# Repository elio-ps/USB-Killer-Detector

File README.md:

# SENTINELLE — détecteur d'USB Killer

SENTINELLE est une **carte électronique**, pas un logiciel. On y branche un périphérique USB suspect, et elle
l'alimente comme le ferait un ordinateur. Pendant ce temps, elle surveille ses lignes **D+**, **D−** et
**VBUS**. Dès qu'une tension anormale apparaît, positive ou négative, un voyant rouge s'allume et **reste
allumé** jusqu'au RESET. Cette tension anormale est la signature d'un USB Killer : ce type de clé charge des
condensateurs sur le 5 V du port, puis les décharge en haute tension sur les lignes du port.

Le périphérique testé n'est relié à aucun ordinateur. La prise USB-C de la carte ne sert qu'à l'alimenter, et
il n'y a rien à installer.

> **État (octobre 2026) :** la v2 est conçue sous KiCad 10, et l'ERC comme le DRC sont propres. Elle n'est pas
> encore fabriquée, ni testée sur une vraie carte : les seuils ci-dessous sont calculés, pas mesurés.

## Utilisation

1. Alimenter la carte par la prise **USB-C** (chargeur 5 V ou port d'ordinateur) : le voyant orange **PWR**
   et le voyant vert **OK** s'allument.
2. Brancher le périphérique à tester sur la prise **USB-A**.
3. Lire les voyants. Un voyant rouge allumé signale une tension anormale sur la ligne correspondante, et le
   voyant vert s'éteint.
4. Appuyer sur **RESET** (ou débrancher l'alimentation) pour effacer l'alarme.

## Fonctionnement (blocs A à H du schéma)

Le schéma est `sch/usb-killer-detector.kicad_sch`.

| Bloc | Rôle | Composants |
|---|---|---|
| **A. Alimentation USB-C (5 V)** | Prise d'alimentation sans lignes de données. Les résistances CC permettent à un chargeur USB-C de fournir le 5 V. Une diode TVS protège le 5 V | J2 (USB4125, 6 broches), R1/R2 5,1 kΩ, D1 SMAJ5.0A, C1/C2, voyant PWR D2 + R3 |
| **B. Port sous test USB-A et protection VBUS** | Fournit le 5 V au périphérique testé. D3 empêche toute tension de remonter vers l'alimentation, F1 (fusible réarmable de 500 mA) coupe en cas de surcharge, et D4 écrête VBUS | J1 (USB-A), D3 SS34, F1 MF-MSMF050-2, D4 SMAJ5.0A |
| **C. Références de seuil VH / VL** | Pont diviseur sur le 5 V : VH = 2,42 V et VL = 0,76 V. Comme ces références suivent le 5 V, les seuils aussi | R4 51 kΩ, R5 33 kΩ, R6 15 kΩ, C3/C4 |
| **D. Étages d'entrée (fenêtre ±)** | Chaque ligne est ramenée dans la plage 0–5 V par un pont à haute impédance. Exemple pour D+ : 2 × 220 kΩ en 1206 (R7 + R8), puis 220 kΩ vers le 5 V et 120 kΩ vers la masse, ce qui donne X = 0,15 × V + 1,5 V. Une BAT54S protège les comparateurs et un condensateur de 1 nF filtre le signal | D+ : R7–R10, C5, D5 ; D− : R11–R14, C6, D6 ; VBUS : R15–R17, C7, D7 |
| **E. Comparateurs LM339** | Deux comparateurs par ligne, l'un pour « trop haut » (X > VH), l'autre pour « trop bas » (X < VL). Leurs sorties à collecteur ouvert sont reliées par paires : l'alarme de chaque ligne est active à l'état bas | U1 (D+, D−), U2 (VBUS + commande du voyant OK ; le 8ᵉ comparateur est inutilisé, entrées fixées) |
| **F. Mémoire d'alarme 74HC279** | Trois bascules R/S. Une alarme, même très brève, fait basculer la sortie Q de la ligne à 1, et elle y reste jusqu'au reset | U3 |
| **G. Voyants** | Chaque sortie Q allume sa LED rouge. Un OU à diodes regroupe les trois alarmes et, par un comparateur de U2, éteint la LED verte | D9/D10/D11 + R22–R24, D12–D14, R25, D15 + R26 |
| **H. Découplage, pull-ups, reset** | 100 nF par circuit intégré et pull-ups des alarmes. Reset à la mise sous tension (R21/C11), décharge de C11 par D8 quand on débranche, bouton RESET | C8–C10, R18–R20, R21, C11, D8, SW1 |

Sur D+ et D−, les entrées présentent environ 440 kΩ : la carte n'absorbe donc pas l'énergie d'une décharge.
Sous −200 V, chaque résistance 1206 voit environ 100 V. Sur le PCB, ces lignes ont 1 mm d'isolation jusqu'aux
résistances d'entrée (règles dans `sch/usb-killer-detector.kicad_dru`).

## Seuils d'alarme

| Ligne | Alarme si | Valeurs calculées |
|---|---|---|
| D+ et D− | **> +6,2 V** ou **< −5 V** | +6,16 V / −4,95 V |
| VBUS | **> +6,3 V** ou **< −0,3 V** | +6,34 V / −0,31 V |

Une ligne USB 2.0 normale ne dépasse pas 3,6 V sur D+/D−, et VBUS reste entre 4,75 et 5,25 V. Le seuil VBUS se
règle avec R16/R17. Calculés avec des résistances à ±1 %, les seuils de D+/D− restent dans une fenêtre d'environ
±0,35 V (voir `docs/bom-jlcpcb.md`). Pour les mesurer sur une carte réelle, suivre
[docs/protocole-test.md](docs/protocole-test.md).

## Voyants

| Voyant | Couleur | Signification |
|---|---|---|
| PWR (D2) | orange | Carte alimentée |
| OK (D15) | vert | Aucune alarme mémorisée |
| D+ (D9) | rouge | Tension anormale vue sur D+ (mémorisée) |
| D− (D10) | rouge | Tension anormale vue sur D− (mémorisée) |
| VBUS (D11) | rouge | Tension anormale vue sur VBUS (mémorisée) |

## Reset

Une alarme reste affichée même si l'anomalie n'a duré qu'un instant : rien ne passe inaperçu en cas de
manque d'attention. Pour l'effacer :
- appuyer sur **RESET** (SW1) : une fois le boîtier mis à jour, on l'atteint avec un trombone par le trou du couvercle ;
- ou débrancher l'alimentation : au rebranchement, les alarmes repartent à zéro.

Si la cause est toujours présente au moment du RESET, l'alarme se rallume aussitôt.

## Fabrication (`sch/production/`)

Ces fichiers sont générés par le plugin KiCad **Fabrication Toolkit** (réglages dans `sch/fabrication-toolkit-options.json`).

| Fichier | Contenu |
|---|---|
| `usb-killer-detector.zip` | Gerber et perçages : **à téléverser chez JLCPCB** |
| `bom.csv` | BOM au format JLCPCB, avec les numéros LCSC vérifiés (LED comprises) : **à téléverser** |
| `positions.csv` | Positions des composants, rotations déjà corrigées pour JLC : **à téléverser** |
| `designators.csv`, `netlist.ipc` | Fichiers annexes du plugin |
| `bom-JLCPCB Assembly Order.xls` | Rapport de rapprochement exporté depuis le site JLC lors d'un premier essai. **Périmé** : il propose encore des 220 kΩ à ±5 % et ne trouve pas les LED. Se fier à `bom.csv` |

Les numéros LCSC sont stockés dans le champ `LCSC Part #` de chaque composant, dans le schéma comme dans le PCB.
Le plugin les reprend donc à chaque régénération. Les rapports ERC et DRC de `kicad-cli` sont dans `sch/rapports/`.

Carte : 2 couches, 44 × 82 mm, 1,6 mm d'épaisseur. **Tout est soudé par le fabricant**, y compris les 5 LED de
5 mm traversantes : il faut donc commander l'assemblage des composants traversants. Choix des références : `docs/bom-jlcpcb.md`.

## Boîtier (`PCB/`)

`PCB/Case/Case.FCStd` et `Lid.FCStd` (FreeCAD), `PCB/Model.3mf` pour l'impression, et
`PCB/SENTINELLE-v2-PCB.step` (modèle 3D de la carte). La vérification des découpes par rapport à la v2 est dans
`docs/boitier-v2.md`.

Le boîtier est à jour pour la v2 : fente USB-A, ouverture USB-C, 5 trous de LED avec tubes guide-lumière, trou
RESET et dégagements sous les broches. Il n'a pas encore été imprimé. Au montage, on retourne le couvercle autour
de son grand axe, encoche de la lèvre côté USB-A.

## Démo

> TODO : vidéo de la carte v2 en fonctionnement.

[`demo.gif`](demo.gif) (30 Mo) montre le **prototype sur breadboard** (v1), testé à l'alimentation de labo.

## Sécurité

Ne jamais brancher la prise USB-A de SENTINELLE sur un ordinateur. Ne pas toucher la carte pendant un test :
la haute tension d'un USB Killer est présente sur la prise USB-A et sur les résistances d'entrée. La validation
se fait sans vrai USB Killer, à l'alimentation de labo (voir le protocole de test).

## Équipe

- Elio Pironneau-Sauranus
- Lucas Rios
- Lenny Gaillard
- Evan Siby

Merci à **Philippe Mege**.

## Licence

GNU GPL v3.0 — voir [LICENSE](LICENSE).

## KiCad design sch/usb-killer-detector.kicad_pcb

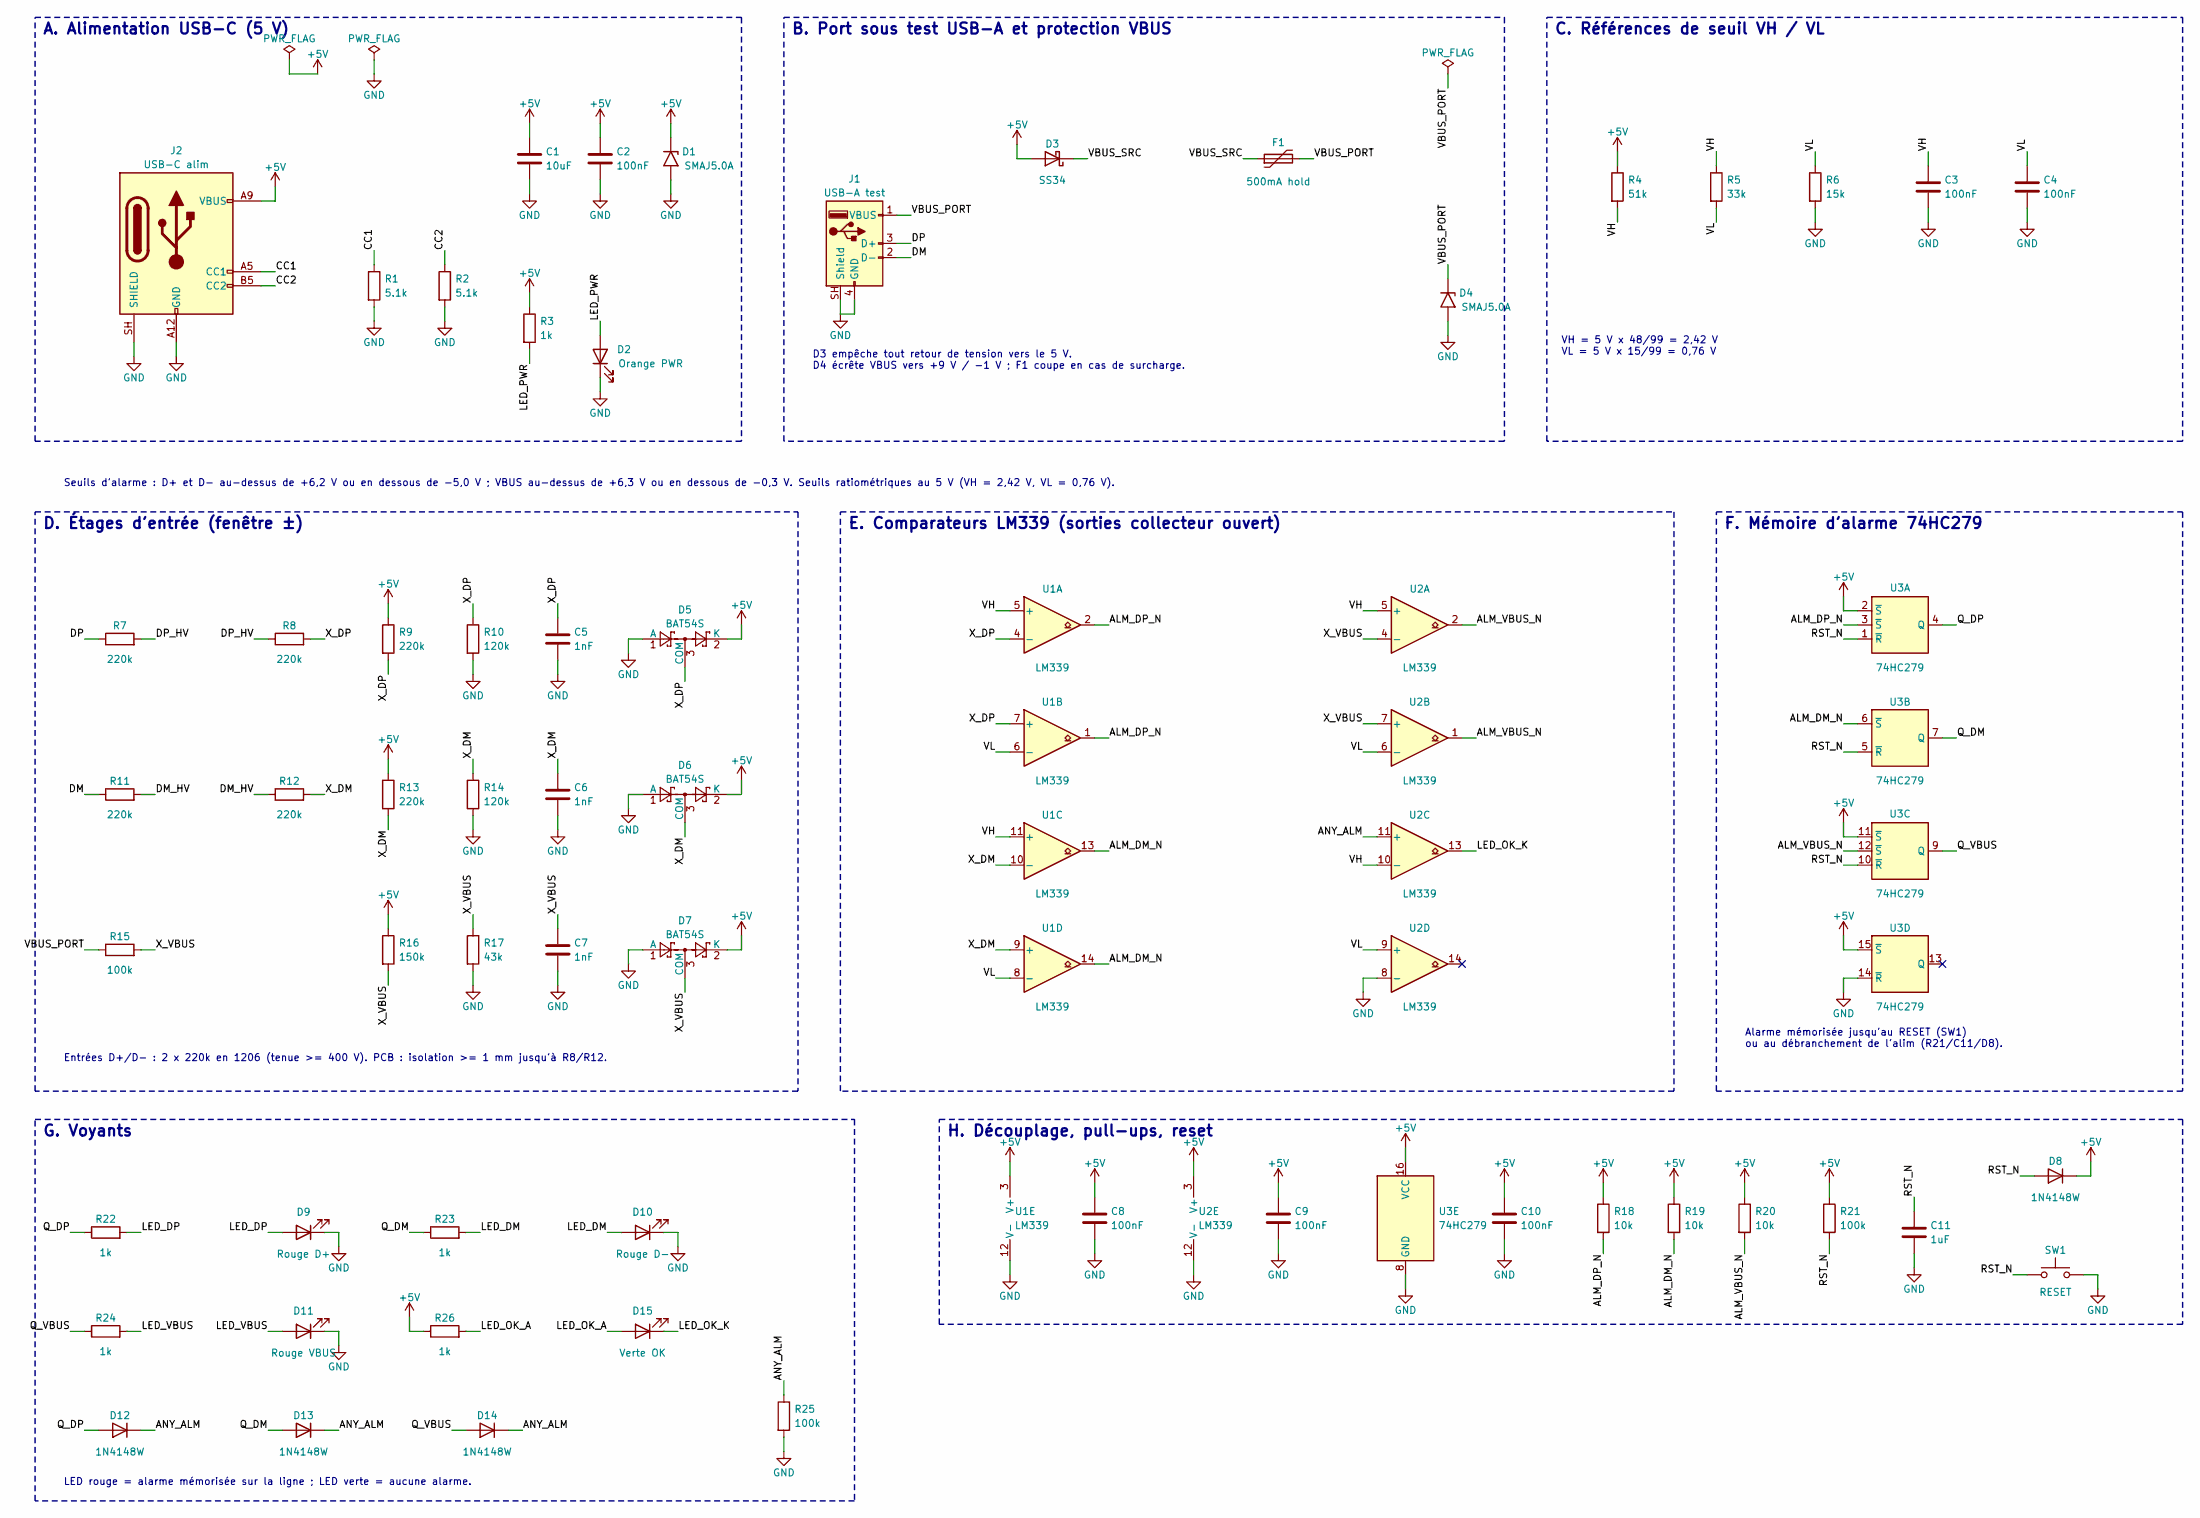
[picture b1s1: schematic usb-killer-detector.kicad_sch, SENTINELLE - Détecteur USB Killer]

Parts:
C1: 10uF; C_0805_2012Metric; LCSC Part # C15850
C2, C3, C4, C8, C9, C10: 100nF; C_0805_2012Metric; LCSC Part # C49678
C5, C6, C7: 1nF; C_0805_2012Metric; LCSC Part # C46653
C11: 1uF; C_0805_2012Metric; LCSC Part # C28323
D1, D4: SMAJ5.0A; D_SMA; MPN SMAJ5.0A; LCSC Part # C113952
D2: Orange PWR; LED_D5.0mm; LCSC Part # C52034657
D3: SS34; D_SMA; MPN SS34; LCSC Part # C8678
D5, D6, D7: BAT54S; SOT-23; MPN BAT54S; LCSC Part # C47546
D8, D12, D13, D14: 1N4148W; D_SOD-123; MPN 1N4148W; LCSC Part # C81598
D9: Rouge D+; LED_D5.0mm; LCSC Part # C87271
D10: Rouge D-; LED_D5.0mm; LCSC Part # C87271
D11: Rouge VBUS; LED_D5.0mm; LCSC Part # C87271
D15: Verte OK; LED_D5.0mm; LCSC Part # C2895548
F1: 500mA hold; Fuse_1812_4532Metric; MPN Bourns MF-MSMF050-2; LCSC Part # C17313
J1: USB-A test; USB_A_Receptacle_GCT_USB1046; MPN GCT USB1046; LCSC Part # C6307429
J2: USB-C alim; USB_C_Receptacle_GCT_USB4125-xx-x_6P_TopMnt_Horizontal; MPN GCT USB4125-GF-A; LCSC Part # C3151650
R1, R2: 5.1k; R_0805_2012Metric; LCSC Part # C27834
R3, R22, R23, R24, R26: 1k; R_0805_2012Metric; LCSC Part # C17513
R4: 51k; R_0805_2012Metric; LCSC Part # C17737
R5: 33k; R_0805_2012Metric; LCSC Part # C17633
R6: 15k; R_0805_2012Metric; LCSC Part # C17475
R7, R8, R11, R12: 220k; R_1206_3216Metric; LCSC Part # C873512
R9, R13: 220k; R_0805_2012Metric; LCSC Part # C17556
R10, R14: 120k; R_0805_2012Metric; LCSC Part # C17436
R15: 100k; R_1206_3216Metric; LCSC Part # C17900
R16: 150k; R_0805_2012Metric; LCSC Part # C17470
R17: 43k; R_0805_2012Metric; LCSC Part # C17695
R18, R19, R20: 10k; R_0805_2012Metric; LCSC Part # C17414
R21, R25: 100k; R_0805_2012Metric; LCSC Part # C149504
SW1: RESET; SW_SPST_B3S-1000; MPN Omron B3S-1000; LCSC Part # C2733655
U1, U2: LM339; SOIC-14_3.9x8.7mm_P1.27mm; MPN LM339DR; LCSC Part # C7948
U3: 74HC279; SOIC-16_3.9x9.9mm_P1.27mm; MPN 74HC279D; LCSC Part # C41430932

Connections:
+5V: C1.1, C2.1, C8.1, C9.1, C10.1, D1.1 (A1), D3.2 (A), D5.2 (K), D6.2 (K), D7.2 (K), D8.1 (K), J2.A9 (VBUS), J2.B9 (VBUS), R3.1, R4.1, R9.1, R13.1, R16.1, R18.1, R19.1, R20.1, R21.1, R26.1, U1.3 (V+), U2.3 (V+), U3.2 (~S), U3.11 (~S), U3.15 (~S), U3.16 (VCC)
/ALM_DM_N: R19.2, U1.13, U1.14, U3.6 (~S)
/ALM_DP_N: R18.2, U1.1, U1.2, U3.3 (~S)
/ALM_VBUS_N: R20.2, U2.1, U2.2, U3.12 (~S)
/ANY_ALM: D12.1 (K), D13.1 (K), D14.1 (K), R25.1, U2.11 (+)
/CC1: J2.A5 (CC1), R1.1
/CC2: J2.B5 (CC2), R2.1
/DM: J1.2 (D-), R11.1
/DM_HV: R11.2, R12.1
/DP: J1.3 (D+), R7.1
/DP_HV: R7.2, R8.1
/LED_DM: D10.2 (A), R23.2
/LED_DP: D9.2 (A), R22.2
/LED_OK_A: D15.2 (A), R26.2
/LED_OK_K: D15.1 (K), U2.13
/LED_PWR: D2.2 (A), R3.2
/LED_VBUS: D11.2 (A), R24.2
/Q_DM: D13.2 (A), R23.1, U3.7 (Q)
/Q_DP: D12.2 (A), R22.1, U3.4 (Q)
/Q_VBUS: D14.2 (A), R24.1, U3.9 (Q)
/RST_N: C11.1, D8.2 (A), R21.2, SW1.1, U3.1 (~R), U3.5 (~R), U3.10 (~R)
/VBUS_PORT: D4.1 (A1), F1.2, J1.1 (VBUS), R15.1
/VBUS_SRC: D3.1 (K), F1.1
/VH: C3.1, R4.2, R5.1, U1.5 (+), U1.11 (+), U2.5 (+), U2.10 (-)
/VL: C4.1, R5.2, R6.1, U1.6 (-), U1.8 (-), U2.6 (-), U2.9 (+)
/X_DM: C6.1, D6.3 (COM), R12.2, R13.2, R14.1, U1.9 (+), U1.10 (-)
/X_DP: C5.1, D5.3 (COM), R8.2, R9.2, R10.1, U1.4 (-), U1.7 (+)
/X_VBUS: C7.1, D7.3 (COM), R15.2, R16.2, R17.1, U2.4 (-), U2.7 (+)
GND: C1.2, C2.2, C3.2, C4.2, C5.2, C6.2, C7.2, C8.2, C9.2, C10.2, C11.2, D1.2 (A2), D2.1 (K), D4.2 (A2), D5.1 (A), D6.1 (A), D7.1 (A), D9.1 (K), D10.1 (K), D11.1 (K), J1.4 (GND), J1.SH (Shield), J2.A12 (GND), J2.B12 (GND), J2.SH (SHIELD), R1.2, R2.2, R6.2, R10.2, R14.2, R17.2, R25.2, SW1.2, U1.12 (V-), U2.8 (-), U2.12 (V-), U3.8 (GND), U3.14 (~R)

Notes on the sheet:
A. Alimentation USB-C (5 V)
B. Port sous test USB-A et protection VBUS
C. Références de seuil VH / VL
D. Étages d'entrée (fenêtre ±)
E. Comparateurs LM339 (sorties collecteur ouvert)
F. Mémoire d'alarme 74HC279
G. Voyants
H. Découplage, pull-ups, reset
Seuils d'alarme : D+ et D- au-dessus de +6,2 V ou en dessous de -5,0 V ; VBUS au-dessus de +6,3 V ou en dessous de -0,3 V. Seuils ratiométriques au 5 V (VH = 2,42 V, VL = 0,76 V).
VH = 5 V x 48/99 = 2,42 V VL = 5 V x 15/99 = 0,76 V
D3 empêche tout retour de tension vers le 5 V. D4 écrête VBUS vers +9 V / -1 V ; F1 coupe en cas de surcharge.
Entrées D+/D- : 2 x 220k en 1206 (tenue >= 400 V). PCB : isolation >= 1 mm jusqu'à R8/R12.
Alarme mémorisée jusqu'au RESET (SW1) ou au débranchement de l'alim (R21/C11/D8).
LED rouge = alarme mémorisée sur la ligne ; LED verte = aucune alarme.

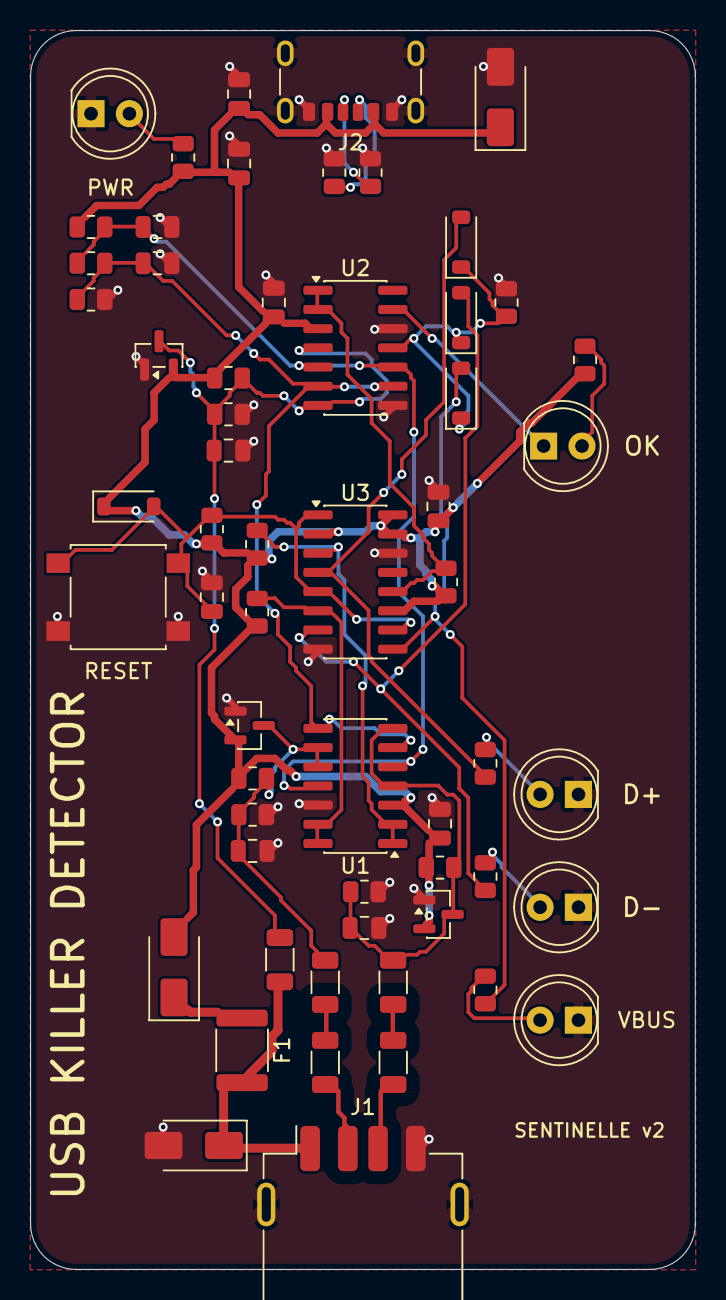
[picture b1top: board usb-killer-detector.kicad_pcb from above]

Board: 2 copper layers, 44.0 x 82.0 mm, 59 parts (0 on the bottom side), 29 nets.

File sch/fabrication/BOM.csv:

"Repere","Valeur","Empreinte","Reference fabricant","Quantite"
"C1","10uF","Capacitor_SMD:C_0805_2012Metric","","1"
"C2,C3,C4,C8,C9,C10","100nF","Capacitor_SMD:C_0805_2012Metric","","6"
"C5,C6,C7","1nF","Capacitor_SMD:C_0805_2012Metric","","3"
"C11","1uF","Capacitor_SMD:C_0805_2012Metric","","1"
"D1,D4","SMAJ5.0A","Diode_SMD:D_SMA","SMAJ5.0A","2"
"D2","Orange PWR","LED_THT:LED_D5.0mm","","1"
"D3","SS34","Diode_SMD:D_SMA","SS34","1"
"D5,D6,D7","BAT54S","Package_TO_SOT_SMD:SOT-23","BAT54S","3"
"D8,D12,D13,D14","1N4148W","Diode_SMD:D_SOD-123","1N4148W","4"
"D9","Rouge D+","LED_THT:LED_D5.0mm","","1"
"D10","Rouge D-","LED_THT:LED_D5.0mm","","1"
"D11","Rouge VBUS","LED_THT:LED_D5.0mm","","1"
"D15","Verte OK","LED_THT:LED_D5.0mm","","1"
"F1","500mA hold","Fuse:Fuse_1812_4532Metric","Bourns MF-MSMF050-2","1"
"J1","USB-A test","Connector_USB:USB_A_Receptacle_GCT_USB1046","GCT USB1046","1"
"J2","USB-C alim","Connector_USB:USB_C_Receptacle_GCT_USB4125-xx-x_6P_TopMnt_Horizontal","GCT USB4125-GF-A","1"
"R1,R2","5.1k","Resistor_SMD:R_0805_2012Metric","","2"
"R3,R22,R23,R24,R26","1k","Resistor_SMD:R_0805_2012Metric","","5"
"R4","51k","Resistor_SMD:R_0805_2012Metric","","1"
"R5","33k","Resistor_SMD:R_0805_2012Metric","","1"
"R6","15k","Resistor_SMD:R_0805_2012Metric","","1"
"R7,R8,R11,R12","220k","Resistor_SMD:R_1206_3216Metric","","4"
"R9,R13","220k","Resistor_SMD:R_0805_2012Metric","","2"
"R10,R14","120k","Resistor_SMD:R_0805_2012Metric","","2"
"R15","100k","Resistor_SMD:R_1206_3216Metric","","1"
"R16","150k","Resistor_SMD:R_0805_2012Metric","","1"
"R17","43k","Resistor_SMD:R_0805_2012Metric","","1"
"R18,R19,R20","10k","Resistor_SMD:R_0805_2012Metric","","3"
"R21,R25","100k","Resistor_SMD:R_0805_2012Metric","","2"
"SW1","RESET","Button_Switch_SMD:SW_SPST_B3S-1000","Omron B3S-1000","1"
"U1,U2","LM339","Package_SO:SOIC-14_3.9x8.7mm_P1.27mm","LM339DR","2"
"U3","74HC279","Package_SO:SOIC-16_3.9x9.9mm_P1.27mm","74HC279D","1"

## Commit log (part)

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2026-06-25 Project
2026-06-25 Reand Me
2026-06-25 PCB: GND
